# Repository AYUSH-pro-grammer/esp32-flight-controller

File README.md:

# ESP32 Flight Controller (Custom PCB)

## Description

This project presents a basic custom flight controller that is based on the ESP32 and MPU6050 IMU chip. The project reads data from the sensors, uses PID control to stabilize the drone, and drives four motors through electronic speed controllers (ESC).

## How PCB will look

## kicad schematic

The repository contains:

* Code for the flight controller
* Code for IMU calibration
* Files with PCB design (KiCad)
* Gerber files for board manufacture

---

## Project Directory Structure

```
flight-controller-code/
├── flightController.ino   # Flight controller code
├── calibration.ino        # IMU calibration code
├── kicad/                 # PCB design files
├── image/                 # Board images
├── main_grb.zip           # Gerber files for fabrication
└── README.md
```

---

## Features

* Integration of MPU6050 accelerometer and gyroscope
* Complementary filter algorithm for angle calculations
* Double-loop PID control (angle and angle rate)
* PWM signals to control 4 ESC motors
* Input from the RC receiver (6 channels)
* IMU calibration for accurate sensor offset values

---

## Hardware Requirements

* ESP32 microcontroller
* MPU6050 IMU
* 4 electronic speed controllers with brushless motors
* RC receiver (PWM protocol)
* LiPo battery
* Custom PCB (designed in KiCad, files in `kicad/` folder)

---

## Setup Procedure

### Step 1 - Upload Calibration Code

1. Load file `calibration.ino`
2. Program ESP32 with this code
3. Put the drone on the ground
4. Open the Serial Monitor window
5. Read instruction messages and save the output values

---

### Step 2 - Fill IMU Offset Values

Fill the calibration values into the file `flightController.ino`:

```
float rateRollOffset = ...;
float ratePitchOffset = ...;
float rateYawOffset = ...;

float accXOffset = ...;
float accYOffset = ...;
float accZOffset = ...;
```

---

### Step 3 - Upload the Main Code

* Load `flightController.ino`
* Program ESP30 with this code

---

## Controls (RC Mapping)

| Channel | Function  |
| ------- | --------- |
| CH1     | Roll      |
| CH2     | Pitch     |
| CH3     | Throttle  |
| CH4     | Yaw       |
| CH5/CH6 | Auxiliary |

---

## Important Tips

* Make sure your motors are installed correctly
* Do not run any tests with propellers mounted
* Fine-tune PID coefficients for better stability
* Calibrate your sensors carefully for optimal results

---

## Safety

* Do not power the motors with mounted propellers
* Ensure reliable power supply
* Have your hand near the throttle button

---

## Possible Upgrades

* Build-in fail-safe system
* Implement altitude hold function
* Enable GPS functionality
* Improve filtering algorithm (Kalman filter)

---

## Reference Code

Key code fragments are found in the following file:

---

## License

This project is open-source and can be freely modified.

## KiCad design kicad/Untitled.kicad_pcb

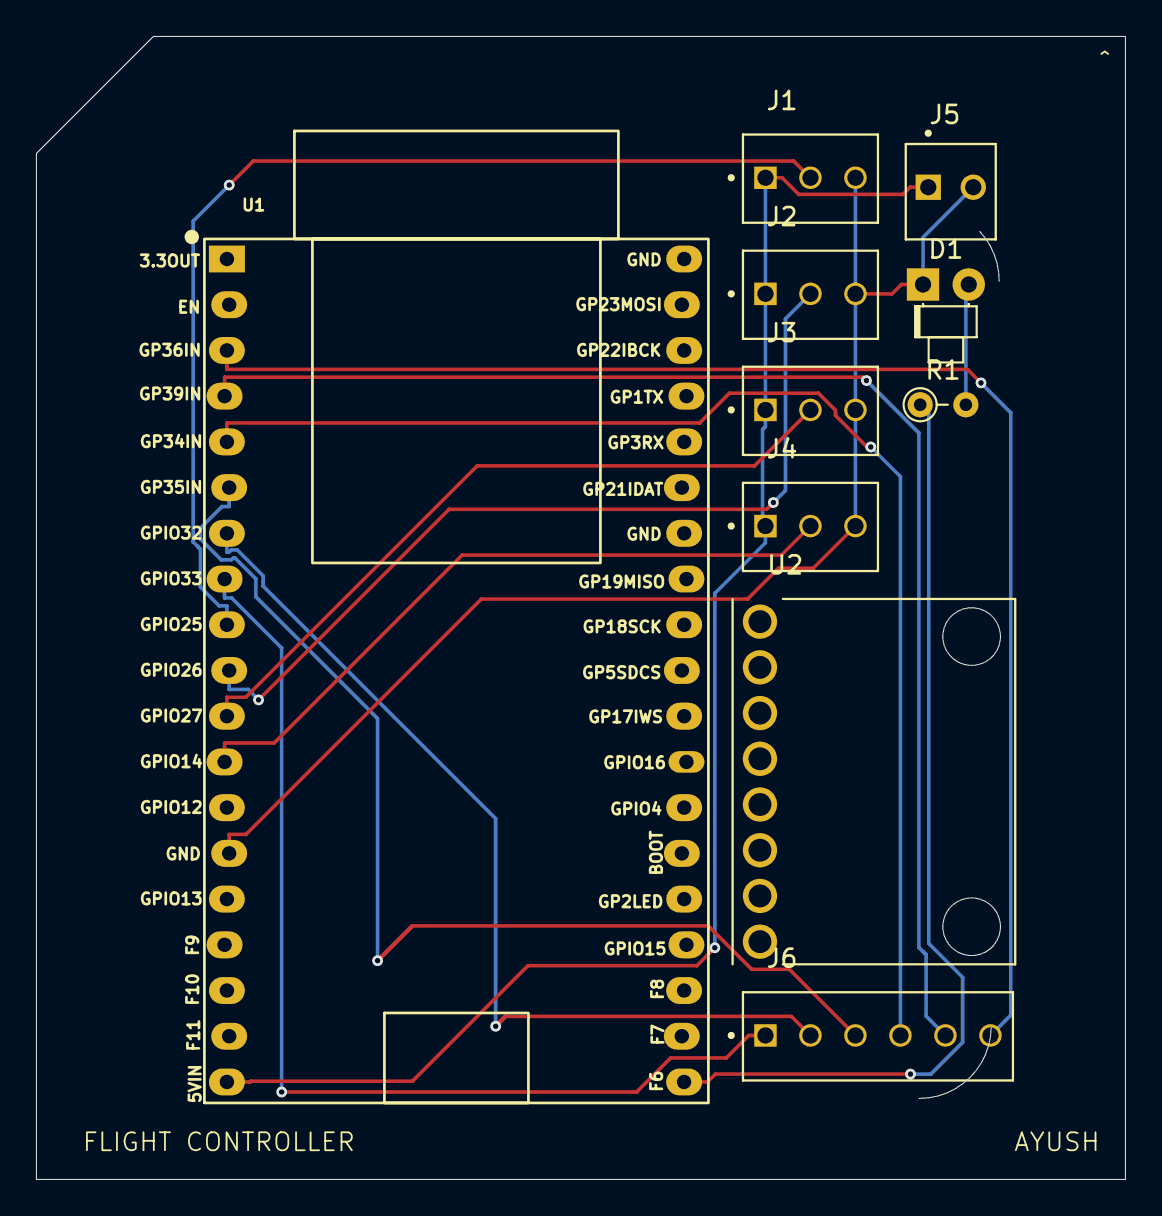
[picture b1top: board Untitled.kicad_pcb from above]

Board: 2 copper layers, 60.5 x 63.5 mm, 10 parts (0 on the bottom side), 14 nets.

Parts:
D1: LED; LED_D1.8mm_W1.8mm_H2.4mm_Horizontal_O1.27mm_Z1.6mm
J1, J2, J3, J4: 2-171825-3; TE_2-171825-3
J5: 171825-2; TE_171825-2
J6: 171825-6; TE_171825-6
R1: R; R_Axial_DIN0204_L3.6mm_D1.6mm_P2.54mm_Vertical
U1: esp32_38_pins-custom_library; Z_ESP32_DevKitC_38pin_socket
U2: MPU-6050; MODULE_GY-521

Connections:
unnamed: D1.2 (A), R1.2
unnamed: J1.1, J2.1, J3.1, J4.1, J5.1, U1.19 (5V)
unnamed: J6.4, U1.5 (GPI34)
unnamed: J6.3, U1.6 (GPI35)
unnamed: J6.6, U1.3 (GPI36)
unnamed: J6.5, U1.4 (GPI39)
unnamed: R1.1, U1.20 (GPIO6)
unnamed: J4.2, U1.12 (GPIO14)
unnamed: J1.2, U1.9 (GPIO25)
unnamed: J2.2, U1.10 (GPIO26)
unnamed: J3.2, U1.11 (GPIO27)
unnamed: J6.2, U1.7 (GPIO32)
unnamed: J6.1, U1.8 (GPIO33)
gnd: D1.1 (K), J1.3, J2.3, J3.3, J4.3, J5.2, U1.14 (GND)

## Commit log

2026-04-16 added code
2026-04-16 added files
2026-04-18 updated pcb
